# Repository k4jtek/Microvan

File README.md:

# Microvan
A Pro Micro powered Minivan layout mechanical keyboard PCB designed by k4jtek. Unfinished yet but the PCB should theoretically work.

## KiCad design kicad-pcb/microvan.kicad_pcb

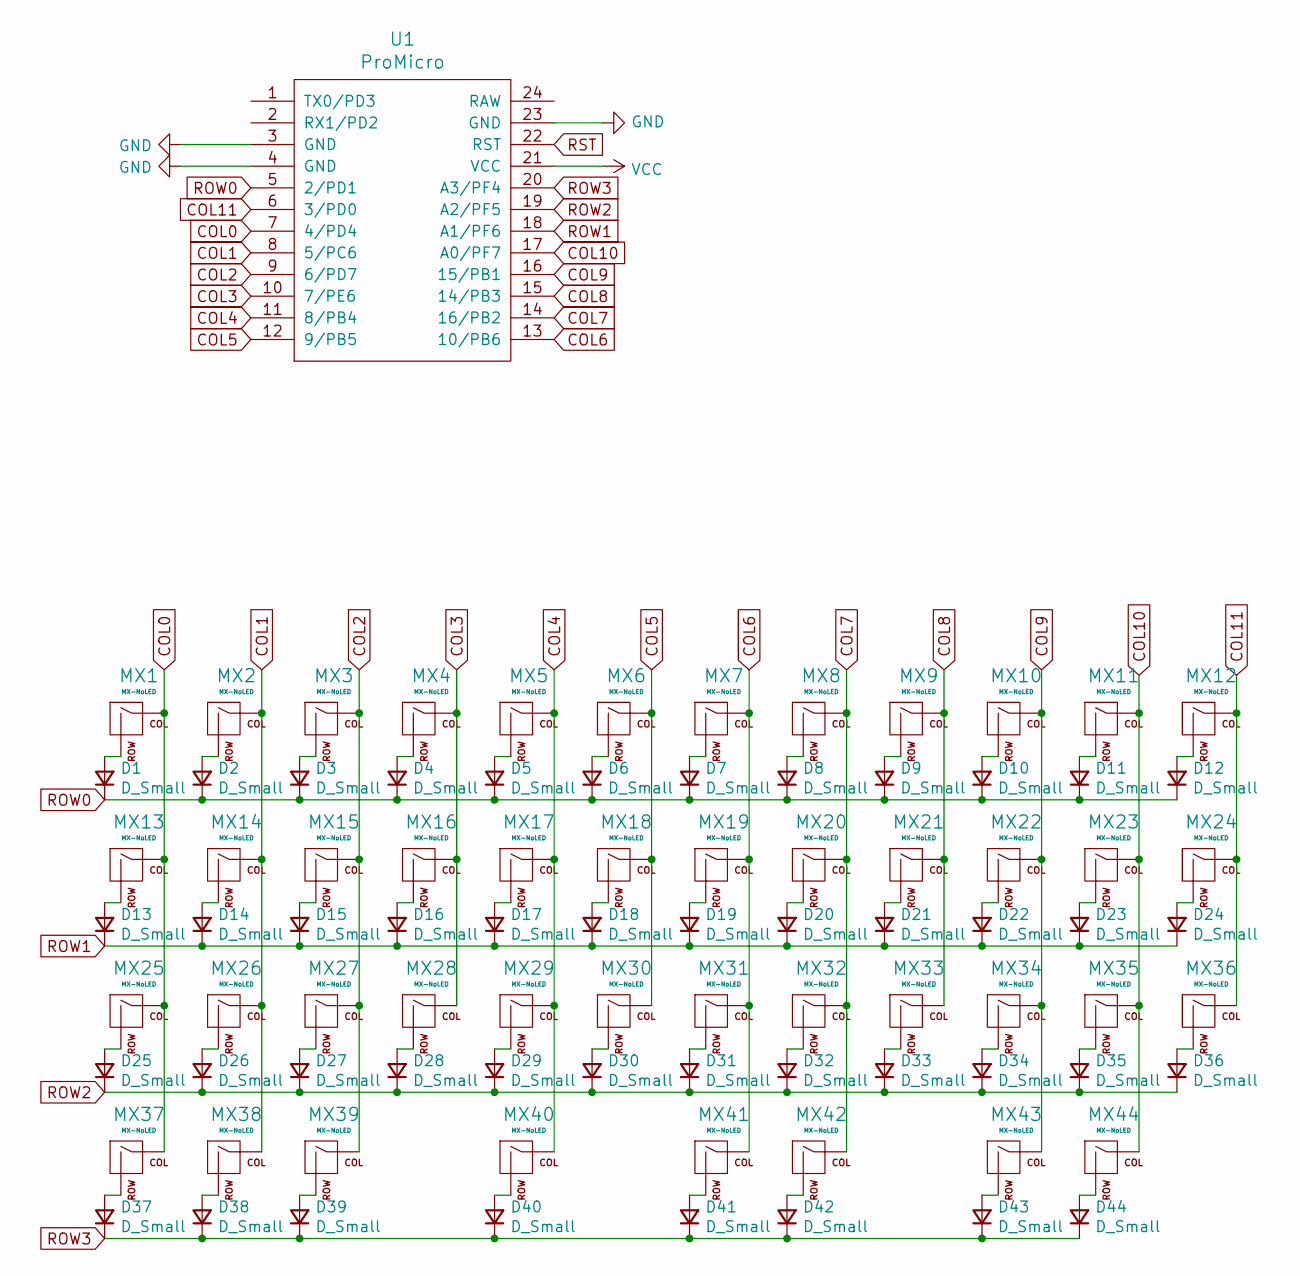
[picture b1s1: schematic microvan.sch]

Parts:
D1, D2, D3, D4, D5, D6, D7, D8, D9, D10, D11, D12, D13, D14, D15, D16, D17, D18, D19, D20, D21, D22, D23, D24, D25, D26, D27, D28, D29, D30, D31, D32, D33, D34, D35, D36, D37, D38, D39, D40, D41, D42, D43, D44: D_Small; Diode-Hybrid-Back
MX1, MX2, MX3, MX4, MX5, MX6, MX7, MX8, MX9, MX10, MX11, MX14, MX15, MX16, MX17, MX18, MX19, MX20, MX21, MX22, MX23, MX26, MX27, MX28, MX29, MX30, MX31, MX32, MX33, MX34, MX35, MX36: MX-NoLED; MX-1U-NoLED
MX12, MX25, MX44: MX-NoLED; MX-1.75U-NoLED
MX13, MX37, MX39, MX42: MX-NoLED; MX-1.25U-NoLED
MX24, MX38, MX43: MX-NoLED; MX-1.5U-NoLED
MX40: MX-NoLED; MX-2.25U-ReversedStabilizers-NoLED
MX41: MX-NoLED; MX-2U-ReversedStabilizers-NoLED
U1: ProMicro; ArduinoProMicro-BackSide

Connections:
COL0: MX1.1 (COL), MX13.1 (COL), MX25.1 (COL), MX37.1 (COL), U1.7 (4/PD4)
COL1: MX2.1 (COL), MX14.1 (COL), MX26.1 (COL), MX38.1 (COL), U1.8 (5/PC6)
COL2: MX3.1 (COL), MX15.1 (COL), MX27.1 (COL), MX39.1 (COL), U1.9 (6/PD7)
COL3: MX4.1 (COL), MX16.1 (COL), MX28.1 (COL), U1.10 (7/PE6)
COL4: MX5.1 (COL), MX17.1 (COL), MX29.1 (COL), MX40.1 (COL), U1.11 (8/PB4)
COL5: MX6.1 (COL), MX18.1 (COL), MX30.1 (COL), U1.12 (9/PB5)
COL6: MX7.1 (COL), MX19.1 (COL), MX31.1 (COL), MX41.1 (COL), U1.13 (10/PB6)
COL7: MX8.1 (COL), MX20.1 (COL), MX32.1 (COL), MX42.1 (COL), U1.14 (16/PB2)
COL8: MX9.1 (COL), MX21.1 (COL), MX33.1 (COL), U1.15 (14/PB3)
COL9: MX10.1 (COL), MX22.1 (COL), MX34.1 (COL), MX43.1 (COL), U1.16 (15/PB1)
COL10: MX11.1 (COL), MX23.1 (COL), MX35.1 (COL), MX44.1 (COL), U1.17 (A0/PF7)
COL11: MX12.1 (COL), MX24.1 (COL), MX36.1 (COL), U1.6 (3/PD0)
GND: U1.3 (GND), U1.4 (GND), U1.23 (GND)
unnamed: D1.2 (A), MX1.2 (ROW)
unnamed: D2.2 (A), MX2.2 (ROW)
unnamed: D3.2 (A), MX3.2 (ROW)
unnamed: D4.2 (A), MX4.2 (ROW)
unnamed: D5.2 (A), MX5.2 (ROW)
unnamed: D6.2 (A), MX6.2 (ROW)
unnamed: D7.2 (A), MX7.2 (ROW)
unnamed: D8.2 (A), MX8.2 (ROW)
unnamed: D9.2 (A), MX9.2 (ROW)
unnamed: D10.2 (A), MX10.2 (ROW)
unnamed: D11.2 (A), MX11.2 (ROW)
unnamed: D12.2 (A), MX12.2 (ROW)
unnamed: D13.2 (A), MX13.2 (ROW)
unnamed: D14.2 (A), MX14.2 (ROW)
unnamed: D15.2 (A), MX15.2 (ROW)
unnamed: D16.2 (A), MX16.2 (ROW)
unnamed: D17.2 (A), MX17.2 (ROW)
unnamed: D18.2 (A), MX18.2 (ROW)
unnamed: D19.2 (A), MX19.2 (ROW)
unnamed: D20.2 (A), MX20.2 (ROW)
unnamed: D21.2 (A), MX21.2 (ROW)
unnamed: D22.2 (A), MX22.2 (ROW)
unnamed: D23.2 (A), MX23.2 (ROW)
unnamed: D24.2 (A), MX24.2 (ROW)
unnamed: D25.2 (A), MX25.2 (ROW)
unnamed: D26.2 (A), MX26.2 (ROW)
unnamed: D27.2 (A), MX27.2 (ROW)
unnamed: D28.2 (A), MX28.2 (ROW)
unnamed: D29.2 (A), MX29.2 (ROW)
unnamed: D30.2 (A), MX30.2 (ROW)
unnamed: D31.2 (A), MX31.2 (ROW)
unnamed: D32.2 (A), MX32.2 (ROW)
unnamed: D33.2 (A), MX33.2 (ROW)
unnamed: D34.2 (A), MX34.2 (ROW)
unnamed: D35.2 (A), MX35.2 (ROW)
unnamed: D36.2 (A), MX36.2 (ROW)
unnamed: D37.2 (A), MX37.2 (ROW)
unnamed: D38.2 (A), MX38.2 (ROW)
unnamed: D39.2 (A), MX39.2 (ROW)
unnamed: D40.2 (A), MX40.2 (ROW)
unnamed: D41.2 (A), MX41.2 (ROW)
unnamed: D42.2 (A), MX42.2 (ROW)
unnamed: D43.2 (A), MX43.2 (ROW)
unnamed: D44.2 (A), MX44.2 (ROW)
ROW0: D1.1 (K), D2.1 (K), D3.1 (K), D4.1 (K), D5.1 (K), D6.1 (K), D7.1 (K), D8.1 (K), D9.1 (K), D10.1 (K), D11.1 (K), D12.1 (K), U1.5 (2/PD1)
ROW1: D13.1 (K), D14.1 (K), D15.1 (K), D16.1 (K), D17.1 (K), D18.1 (K), D19.1 (K), D20.1 (K), D21.1 (K), D22.1 (K), D23.1 (K), D24.1 (K), U1.18 (A1/PF6)
ROW2: D25.1 (K), D26.1 (K), D27.1 (K), D28.1 (K), D29.1 (K), D30.1 (K), D31.1 (K), D32.1 (K), D33.1 (K), D34.1 (K), D35.1 (K), D36.1 (K), U1.19 (A2/PF5)
ROW3: D37.1 (K), D38.1 (K), D39.1 (K), D40.1 (K), D41.1 (K), D42.1 (K), D43.1 (K), D44.1 (K), U1.20 (A3/PF4)

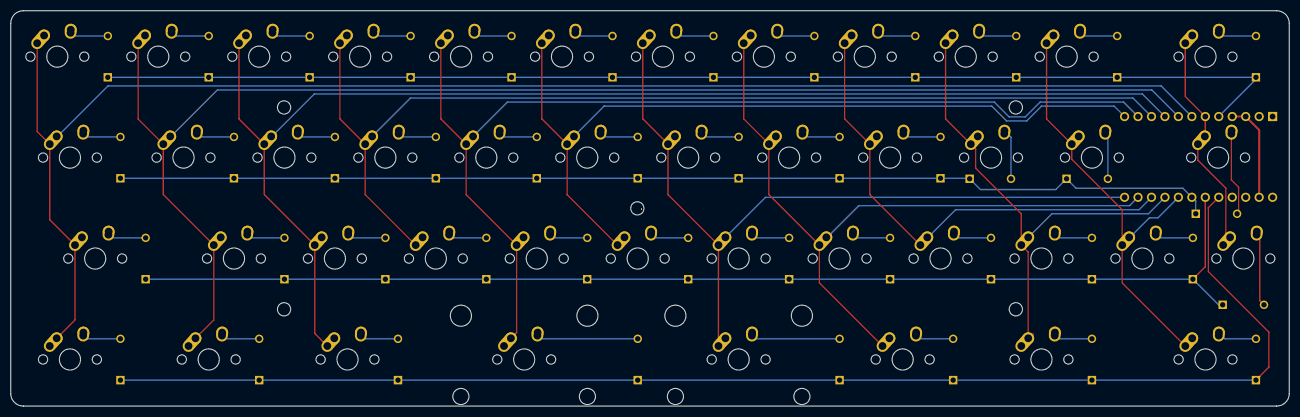
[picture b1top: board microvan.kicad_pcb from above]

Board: 2 copper layers, 241.3 x 74.6 mm, 90 parts (0 on the bottom side), 61 nets.

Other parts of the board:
.: MountingHole_2.5mm

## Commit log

2021-09-28 Added Kicad project.
2021-09-28 Create LICENSE
2021-09-28 Added .gitignore
2021-09-28 Add libraries
2021-09-28 some fix
2021-10-06 Add kicad schematic
2021-10-07 Add footprints and routing to PCB file
2021-10-10 Fix routing and add edge cuts.
2021-10-15 Some changes to the PCB.
2021-10-15 Add some pictures
2021-10-15 Add mounting holes
2021-10-15 Add case files
